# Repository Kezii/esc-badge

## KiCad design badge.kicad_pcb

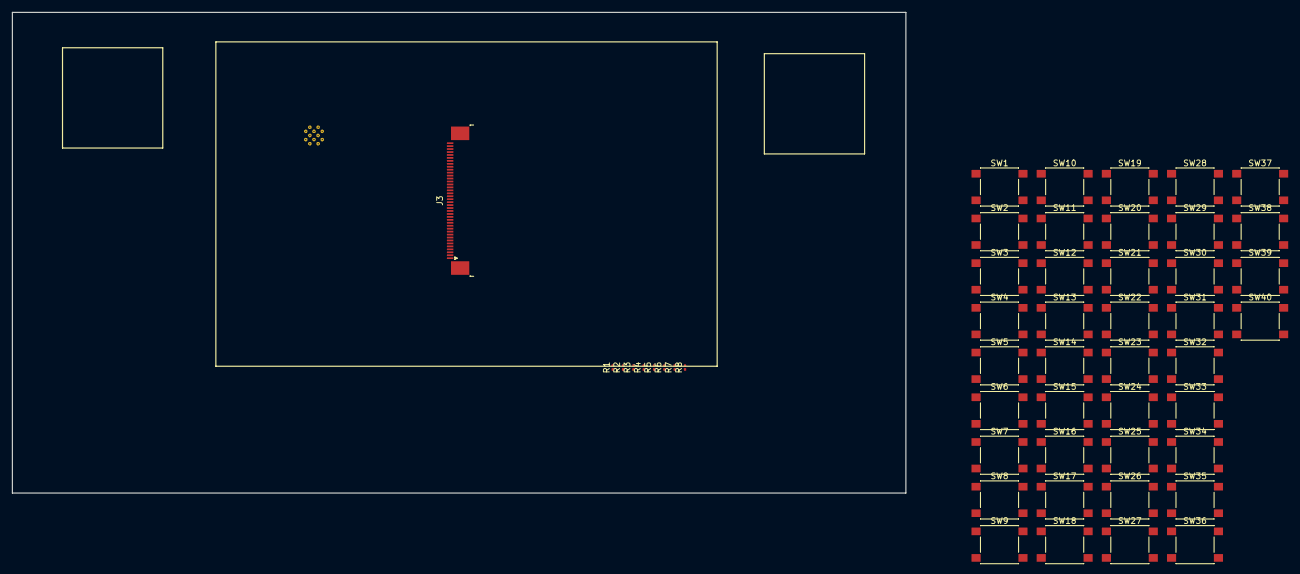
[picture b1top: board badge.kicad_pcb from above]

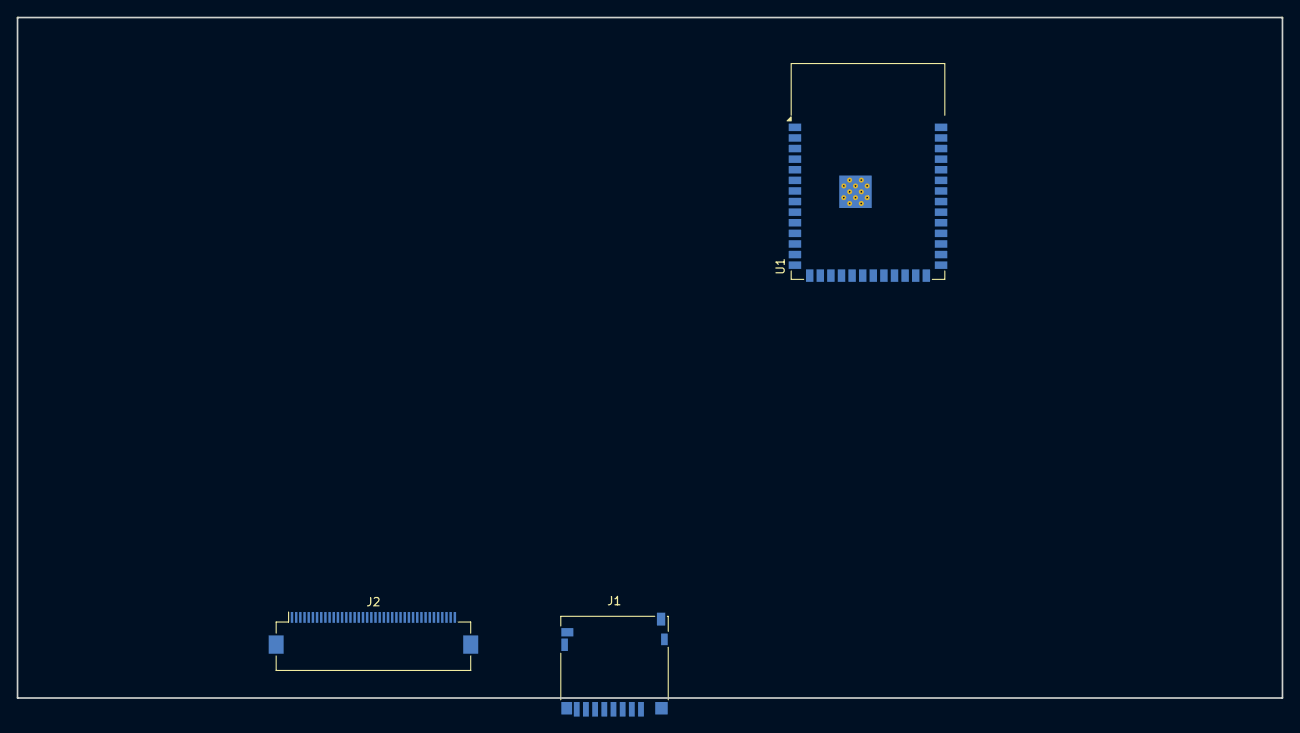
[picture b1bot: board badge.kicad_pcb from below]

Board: 2 copper layers, 151.5 x 81.5 mm, 52 parts (3 on the bottom side), 9 nets, no tracks yet.

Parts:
J1: Micro_SD_Card; microSD_HC_Hirose_DM3D-SF
J2: Conn_01x40; Hirose_FH12-40S-0.5SH_1x40-1MP_P0.50mm_Horizontal
J3: Conn_01x40; TE_4-1734839-0_1x40-1MP_P0.5mm_Horizontal
R1, R2: R; R_0201_0603Metric
R3, R4, R5, R6, R7, R8: 10k; R_0201_0603Metric
SW1, SW2, SW3, SW4, SW5, SW6, SW7, SW8, SW9, SW10, SW11, SW12, SW13, SW14, SW15, SW16, SW17, SW18, SW19, SW20, SW21, SW22, SW23, SW24, SW25, SW26, SW27, SW28, SW29, SW30, SW31, SW32, SW33, SW34, SW35, SW36, SW37, SW38, SW39, SW40: SW_Push; SW_Push_1P1T_NO_6x6mm_H9.5mm
U1: ESP32-S3-WROOM-1

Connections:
+3.3V: J1.4 (VDD), R3.1, R4.1, R5.1, R6.1, R7.1, R8.1
/mcu/SD_CLK: J1.5 (CLK), R5.2
/mcu/SD_CMD: J1.3 (CMD), R6.2
/mcu/SD_D0: J1.7 (DAT0), R4.2
GND: J1.6 (VSS), J1.9 (SHIELD), R1.2, R2.2
unnamed: J1.8 (DAT1), R3.2
unnamed: J1.1 (DAT2), R8.2
unnamed: J1.2 (DAT3/CD), R7.2
unnamed: U1.1 (GND), U1.40 (GND), U1.41 (GND)

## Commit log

2024-03-26 init
2024-03-26 add sensors sheet
2024-04-07 add buck and power switch
